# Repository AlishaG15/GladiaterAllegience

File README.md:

# GladiaterAllegience

A custom wireless transmitter/receiver system built around the **ESP32-C3** and **nRF24L01** 2.4 GHz radio module, with fully custom PCBs designed in KiCad.

---

## Overview

GladiaterAllegience is a hardware project consisting of two paired PCB modules:

- **TransmitterModule** — a handheld controller with buttons and potentiometers that sends commands over nRF24L01 RF
- **ReceiverModule** — the on-device board that receives those commands and drives outputs (LEDs, servos, etc.)

Firmware runs on the ESP32-C3 and is written in Arduino/C++.

---

## Repository Structure

```
GladiaterAllegience/
│
├── TransmitterModule/                  # KiCad PCB project — handheld transmitter (current)
│   ├── sgh24_TransmitterModule.kicad_pro
│   ├── sgh24_TransmitterModule.kicad_sch
│   ├── sgh24_TransmitterModule.kicad_pcb
│   ├── sgh24_TransmitterModule.step    # 3D model export
│   └── Transmitter Output Files/       # Gerbers + drill files ready for fabrication
│
├── ReceiverModule_V1/                  # KiCad PCB project — receiver board (v1)
│   ├── ReceiverModule.kicad_pro
│   ├── ReceiverModule.kicad_sch
│   └── ReceiverModule.kicad_pcb
│
├── ReceiverModule_V2/                  # KiCad PCB project — receiver board (v2, current)
│   ├── ReceiverModule_V2.kicad_pro
│   ├── ReceiverModule_V2.kicad_sch
│   └── ReceiverModule_V2.kicad_pcb
│
├── TranceiverV1_Circuit/               # KiCad PCB project — early combined transceiver board
│   ├── TranceiverV1.kicad_pro
│   ├── TranceiverV1.kicad_sch
│   └── TranceiverV1.kicad_pcb
│
├── ESP32C3_Transmitter_Receiver_Arduino/
│   ├── Transmitter_V2/
│   │   └── Gladiator_Transmitter_V2/   # ESP32-C3 transmitter firmware
│   └── Receiver_V2/
│       └── Gladiator_Receiver_V2/      # ESP32-C3 receiver firmware
│
├── ESP32C3_Servo_Arduino/
│   └── Gladiator_Allegiance_Servo/     # ESP32-C3 servo control firmware
│
├── ESP32C3_Servo_Receiver_Final_Arduino/
│   └── ESP32C3_Final_Receiver/         # Final receiver firmware with servo output
│
├── Components/                         # KiCad custom component library
│   ├── NRF24L01_/                      # nRF24L01 symbol + footprint + 3D model
│   ├── 102010388/                      # Seeed XIAO ESP32-C3 symbol + footprint
│   ├── ATE1D-2M3-10-Z/                # Relay symbol + footprint + 3D model
│   └── TS02_66_50_BK_100_LCR_D/      # Tactile button symbol + footprint
│
├── ServoArduino_V1/
│   └── servo_sweep_test/               # Early servo sweep test (Arduino Uno)
│
└── Arduino_NRF24_Test/
    └── ReceiverModule/                 # Early nRF24L01 receiver proof-of-concept
```

---

## Hardware

| Module | MCU | Radio | Key components |
|---|---|---|---|
| Transmitter | ESP32-C3 (Seeed XIAO) | nRF24L01 | Buttons, potentiometers |
| Receiver V1 | ESP32-C3 (Seeed XIAO) | nRF24L01 | LED outputs |
| Receiver V2 | ESP32-C3 (Seeed XIAO) | nRF24L01 | LED outputs + servo |

PCBs are designed in **KiCad 8**. Fabrication-ready Gerbers for the transmitter are in `TransmitterModule/Transmitter Output Files/`.

---

## Firmware

### Transmitter (`ESP32C3_Transmitter_Receiver_Arduino/Transmitter_V2/Gladiator_Transmitter_V2/`)

Reads a button (active LOW) and transmits over nRF24L01 when pressed. Blinks an LED on successful TX.

**Dependencies:** `RF24` library

### Receiver (`ESP32C3_Transmitter_Receiver_Arduino/Receiver_V2/Gladiator_Receiver_V2/`)

Listens on the nRF24L01 address and drives LED outputs. Uses a button-triggered state machine to control eye and nose LED brightness/blink rate from potentiometer readings.

**Dependencies:** `RF24` library

### Servo + Final Receiver (`ESP32C3_Servo_Arduino/` and `ESP32C3_Servo_Receiver_Final_Arduino/`)

Servo control firmware and the final integrated receiver that combines RF reception with servo output.

**Dependencies:** `RF24` library, `Servo` library

### Flashing

1. Install the [ESP32 board package](https://docs.espressif.com/projects/arduino-esp32/en/latest/installing.html) in Arduino IDE
2. Select board: **XIAO_ESP32C3**
3. Install the `RF24` library via Library Manager
4. Open the `.ino` file and upload

---

## KiCad Setup

Custom component libraries are stored in `Components/`. To use them:

1. Open KiCad → Preferences → Manage Symbol Libraries → Add the `.kicad_sym` files
2. Open KiCad → Preferences → Manage Footprint Libraries → Add the `.kicad_mod` files

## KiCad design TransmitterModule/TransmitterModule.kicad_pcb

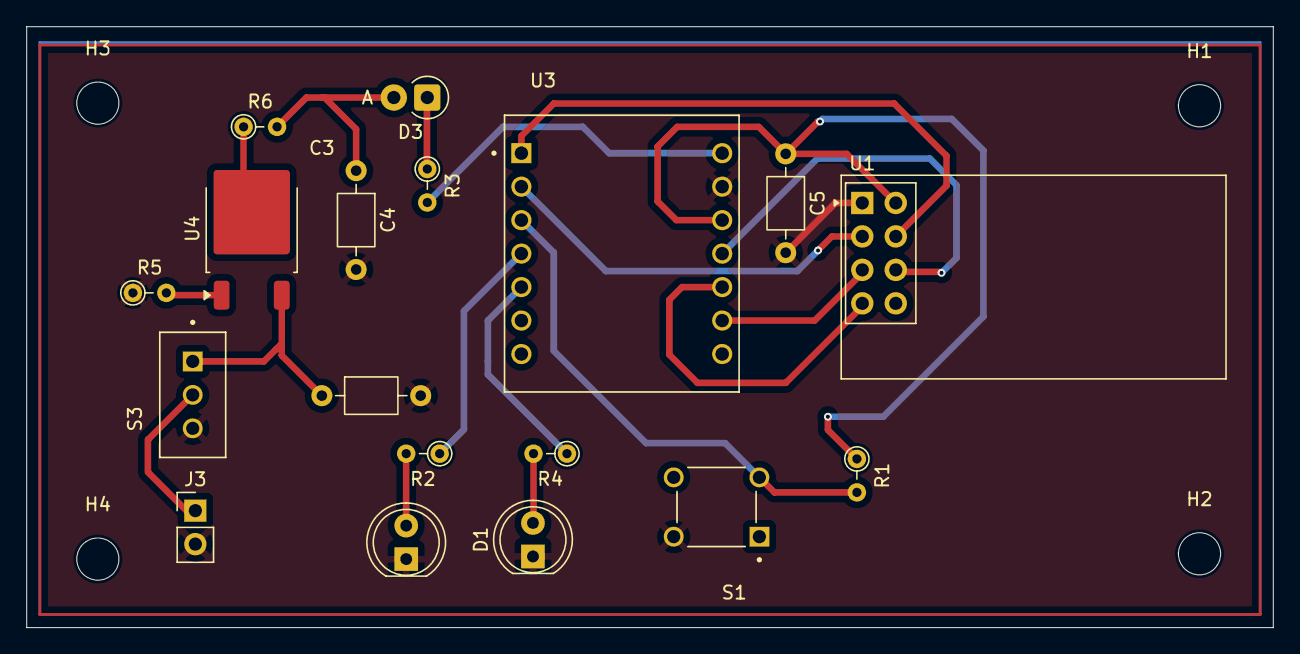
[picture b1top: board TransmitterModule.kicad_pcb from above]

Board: 2 copper layers, 94.6 x 45.6 mm, 22 parts (0 on the bottom side), 19 nets.

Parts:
C3: 10u; C_Axial_L3.8mm_D2.6mm_P7.50mm_Horizontal
C4: 22u; C_Axial_L3.8mm_D2.6mm_P7.50mm_Horizontal
C5: 100u; C_Axial_L3.8mm_D2.6mm_P7.50mm_Horizontal
D1, D2: LED; LED_D5.0mm
D3: D_Schottky; D_T-1_P2.54mm_Vertical_AnodeUp
H1, H2, H3, H4: MountingHole; MountingHole_3.2mm_M3
J3: Battery; PinHeader_1x02_P2.54mm_Vertical
R1, R2, R3, R4: 1k; R_Axial_DIN0204_L3.6mm_D1.6mm_P2.54mm_Vertical
R5: 360; R_Axial_DIN0204_L3.6mm_D1.6mm_P2.54mm_Vertical
R6: 120; R_Axial_DIN0204_L3.6mm_D1.6mm_P2.54mm_Vertical
S1: TS02-66-50-BK-100-LCR-D; SW_TS02-66-50-BK-100-LCR-D
S3: ATE1D-2M3-10-Z; SW_ATE1D-2M3-10-Z
U1: NRF24L01_; nRF24L01_Breakout
U3: 102010388; MODULE_102010388
U4: LD1086DTTR; TO-252-2

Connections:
/5V_IN: R3.2, U3.14 (5V)
/CE: U1.3, U3.2 (PA4_A1_D1)
/CSN: U1.4, U3.1 (PA02_A0_D0)
/DIG_IN: R1.2, S1.3, U3.3 (PA10_A2_D2)
/LED_ON1: R2.1, U3.4 (PA11_A3_D3)
/LED_ON2: R4.1, U3.5 (PA8_A4_D4_SDA)
/MISO: U1.7, U3.10 (PA5_A9_D9_MISO)
/MOSI: U1.6, U3.11 (PA6_A10_D10_MOSI)
/Regulator_In: C3.1, S3.1, U4.3 (IN)
/SCK: U1.5, U3.9 (PA7_A8_D8_SCK)
/VCC: C5.1, R1.1, U1.2, U3.12 (3V3)
GND: C3.2, C4.2, C5.2, D1.1 (K), D2.1 (K), J3.2, R5.1, S1.2, S3.3, U1.1, U3.13 (GND)
unnamed: D1.2 (A), R4.2
unnamed: D2.2 (A), R2.2
unnamed: C4.1, D3.2 (A), R6.2
unnamed: D3.1 (K), R3.1
unnamed: J3.1, S3.2
unnamed: R5.2, U4.1 (ADJ/GND)
unnamed: R6.1, U4.2 (OUT)

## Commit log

2026-03-05 arduino files receiver and servo
2026-03-31 changed switch
2026-03-31 rewired traces and changed diode position added mounting holes
2026-04-01 added transmitter module
2026-04-01 added net id and name
2026-04-13 Added ESP32C3 Transmitter and Receiver Firmware
2026-04-14 added new firmware and pcb files
2026-04-29 chore: clean up repo for readability and professionalism
    - Add .gitignore for KiCad (backups, lock files, prl, fp-info-cache) and macOS (.DS_Store)
    - Remove all .DS_Store, .lck, and fp-info-cache files from tracking
    - Untrack KiCad *-backups/ folders (kept on disk) and loose .zip duplicates
    - Remove nested duplicate subdirs (ReceiverModule/ReceiverModule, TransmitterModule/TransmitterModule)
    - Remove duplicate NRF24L01_ copy component folder
    - Rename 'Arduino Testing 3:5:26' → Arduino_NRF24_Test (colon-safe, descriptive)
2026-04-29 chore: cleanup round 2 after merge
    - Untrack all KiCad-generated files (fp-info-cache, .kicad_prl, backups, lock files, autosave)
    - Remove TransceiverV2 (duplicate of TranceiverV1_Circuit from merge conflict)
    - Remove ServoArduino_V1/sketch_mar5d (duplicate of servo_sweep_test)
    - Remove old Gladiator_Transmitter_Final_20260412205739 folder (superseded by Gladiator_Transmitter_V2)
    - Remove loose sketch_apr9a.ino and sketch_apr9a/ folder (superseded by Gladiator_Receiver_V2)
    - Remove TransmitterModule/TransmitterModule nested subfolder
